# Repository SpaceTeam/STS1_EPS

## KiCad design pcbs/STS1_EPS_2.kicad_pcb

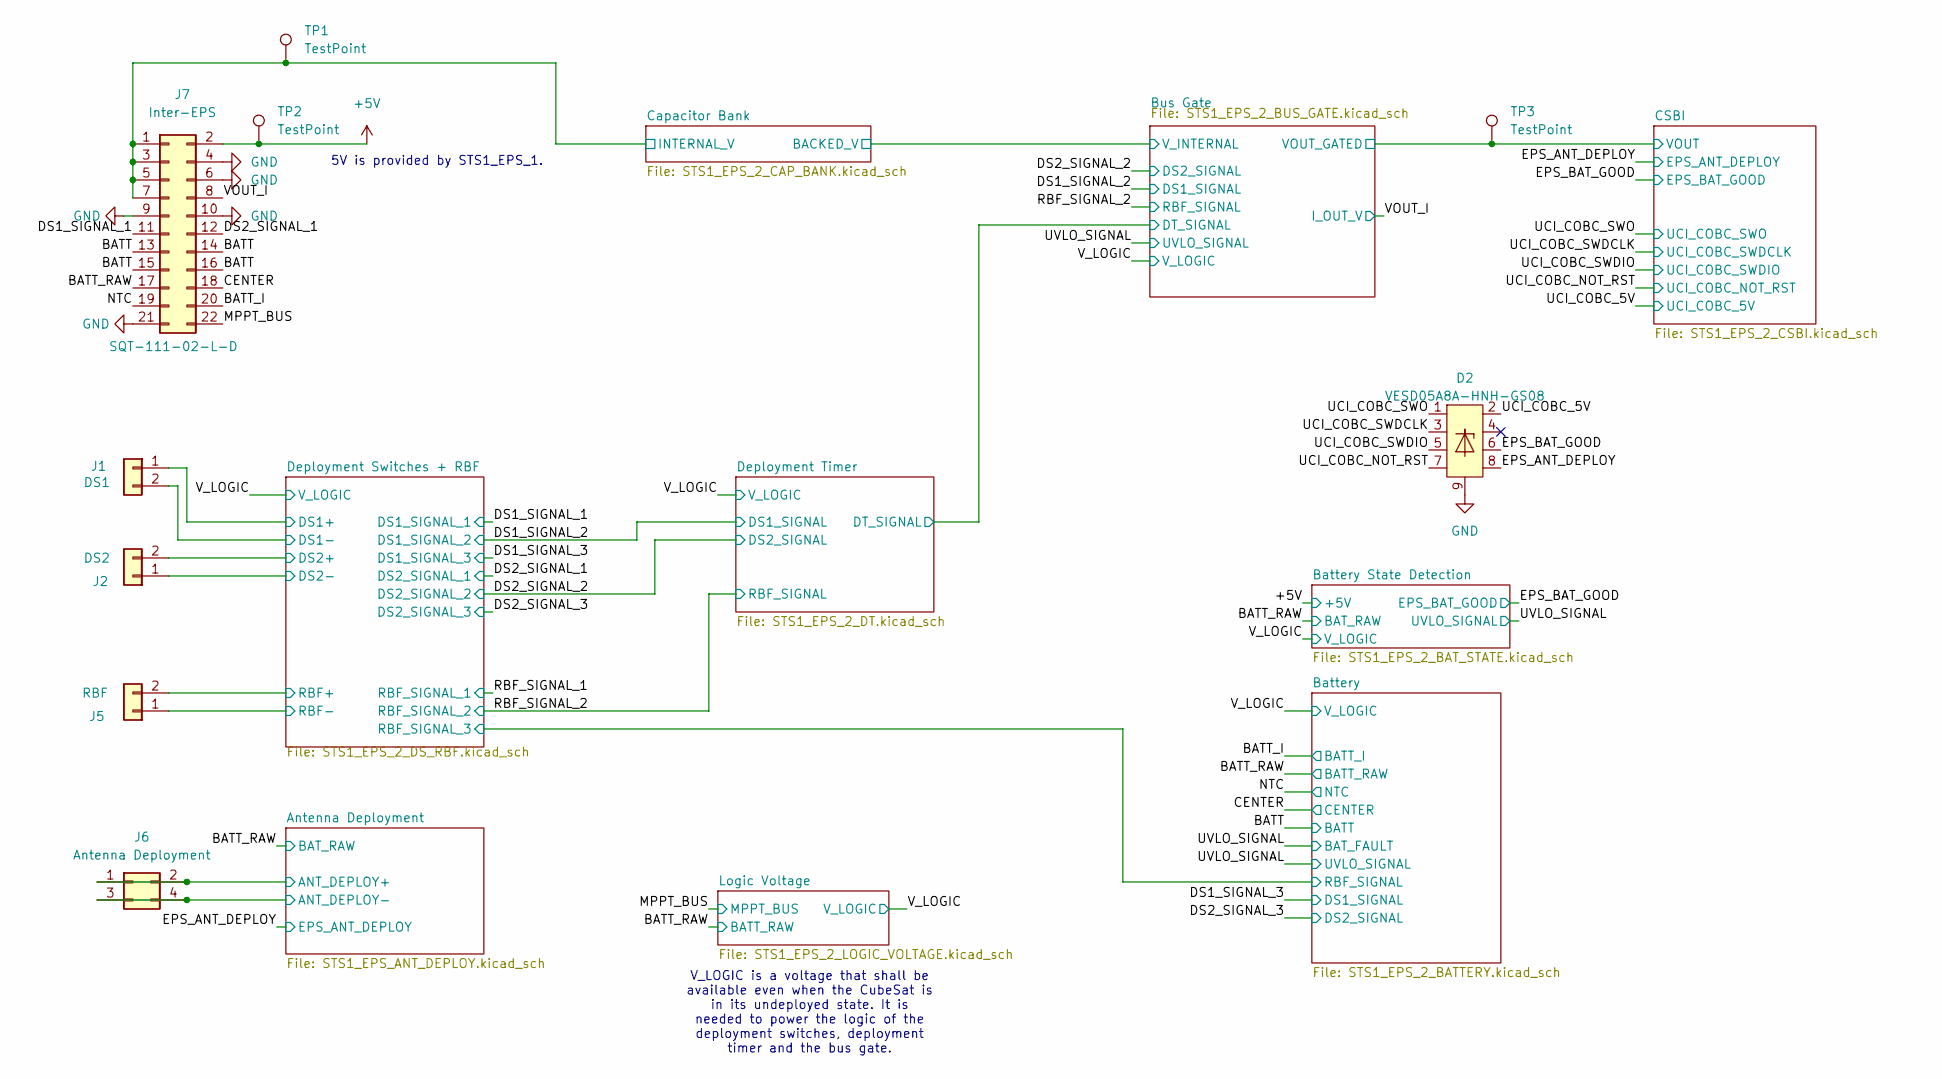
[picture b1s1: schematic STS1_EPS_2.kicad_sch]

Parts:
D2: VESD05A8A-HNH-GS08; LLP1713-9L
J1: DS1; M808420245; Part Nr. M80-8420245
J2: DS2; M808420245; Part Nr. M80-8420245
J5: RBF; M808420245; Part Nr. M808420245
J6: Antenna Deployment; SAMTEC_T1M-04-X-SV-L; Part Nr. SAMTEC T1M-04-X-SV-L
J7: Inter-EPS; PinHeader_2x11_P2.00mm_Vertical; Part# SQT-111-02-L-D
TP1, TP2, TP3: TestPoint; TestPoint_THTPad_D1.0mm_Drill0.5mm

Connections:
+5V: J7.2, TP2.1 (1_1); also elsewhere on the board
/Antenna Deployment/ANT_DEPLOY-: J6.3, J6.4; also elsewhere on the board
/BATT: J7.13, J7.14, J7.15, J7.16; also elsewhere on the board
/BATT_I: J7.20; also elsewhere on the board
/BATT_RAW: J6.1, J6.2, J7.17; also elsewhere on the board
/Bus Gate/VOUT_GATED: TP3.1 (1_1); also elsewhere on the board
/Bus Gate/V_INTERNAL: J7.1, J7.3, J7.5, J7.7, TP1.1 (1_1); also elsewhere on the board
/CENTER: J7.18; also elsewhere on the board
/DS1_SIGNAL_1: J7.11; also elsewhere on the board
/DS2_SIGNAL_1: J7.12; also elsewhere on the board
/Deployment Switches + RBF/DS1+: J1.1; also elsewhere on the board
/Deployment Switches + RBF/DS2+: J2.2; also elsewhere on the board
/Deployment Switches + RBF/RBF-: J5.1; also elsewhere on the board
/EPS_ANT_DEPLOY: D2.8; also elsewhere on the board
/EPS_BAT_GOOD: D2.6; also elsewhere on the board
/MPPT_BUS: J7.22; also elsewhere on the board
/NTC: J7.19; also elsewhere on the board
/UCI_COBC_5V: D2.2; also elsewhere on the board
/UCI_COBC_NOT_RST: D2.7; also elsewhere on the board
/UCI_COBC_SWDCLK: D2.3; also elsewhere on the board
/UCI_COBC_SWDIO: D2.5; also elsewhere on the board
/UCI_COBC_SWO: D2.1; also elsewhere on the board
/VOUT_I: J7.8; also elsewhere on the board
/V_LOGIC: J5.2; also elsewhere on the board
GND: D2.9, J1.2, J2.1, J7.4, J7.6, J7.9, J7.10, J7.21; also elsewhere on the board

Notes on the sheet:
5V is provided by STS1_EPS_1.
V_LOGIC is a voltage that shall be available even when the CubeSat is in its undeployed state. It is needed to power the logic of the deployment switches, deployment timer and the bus gate.

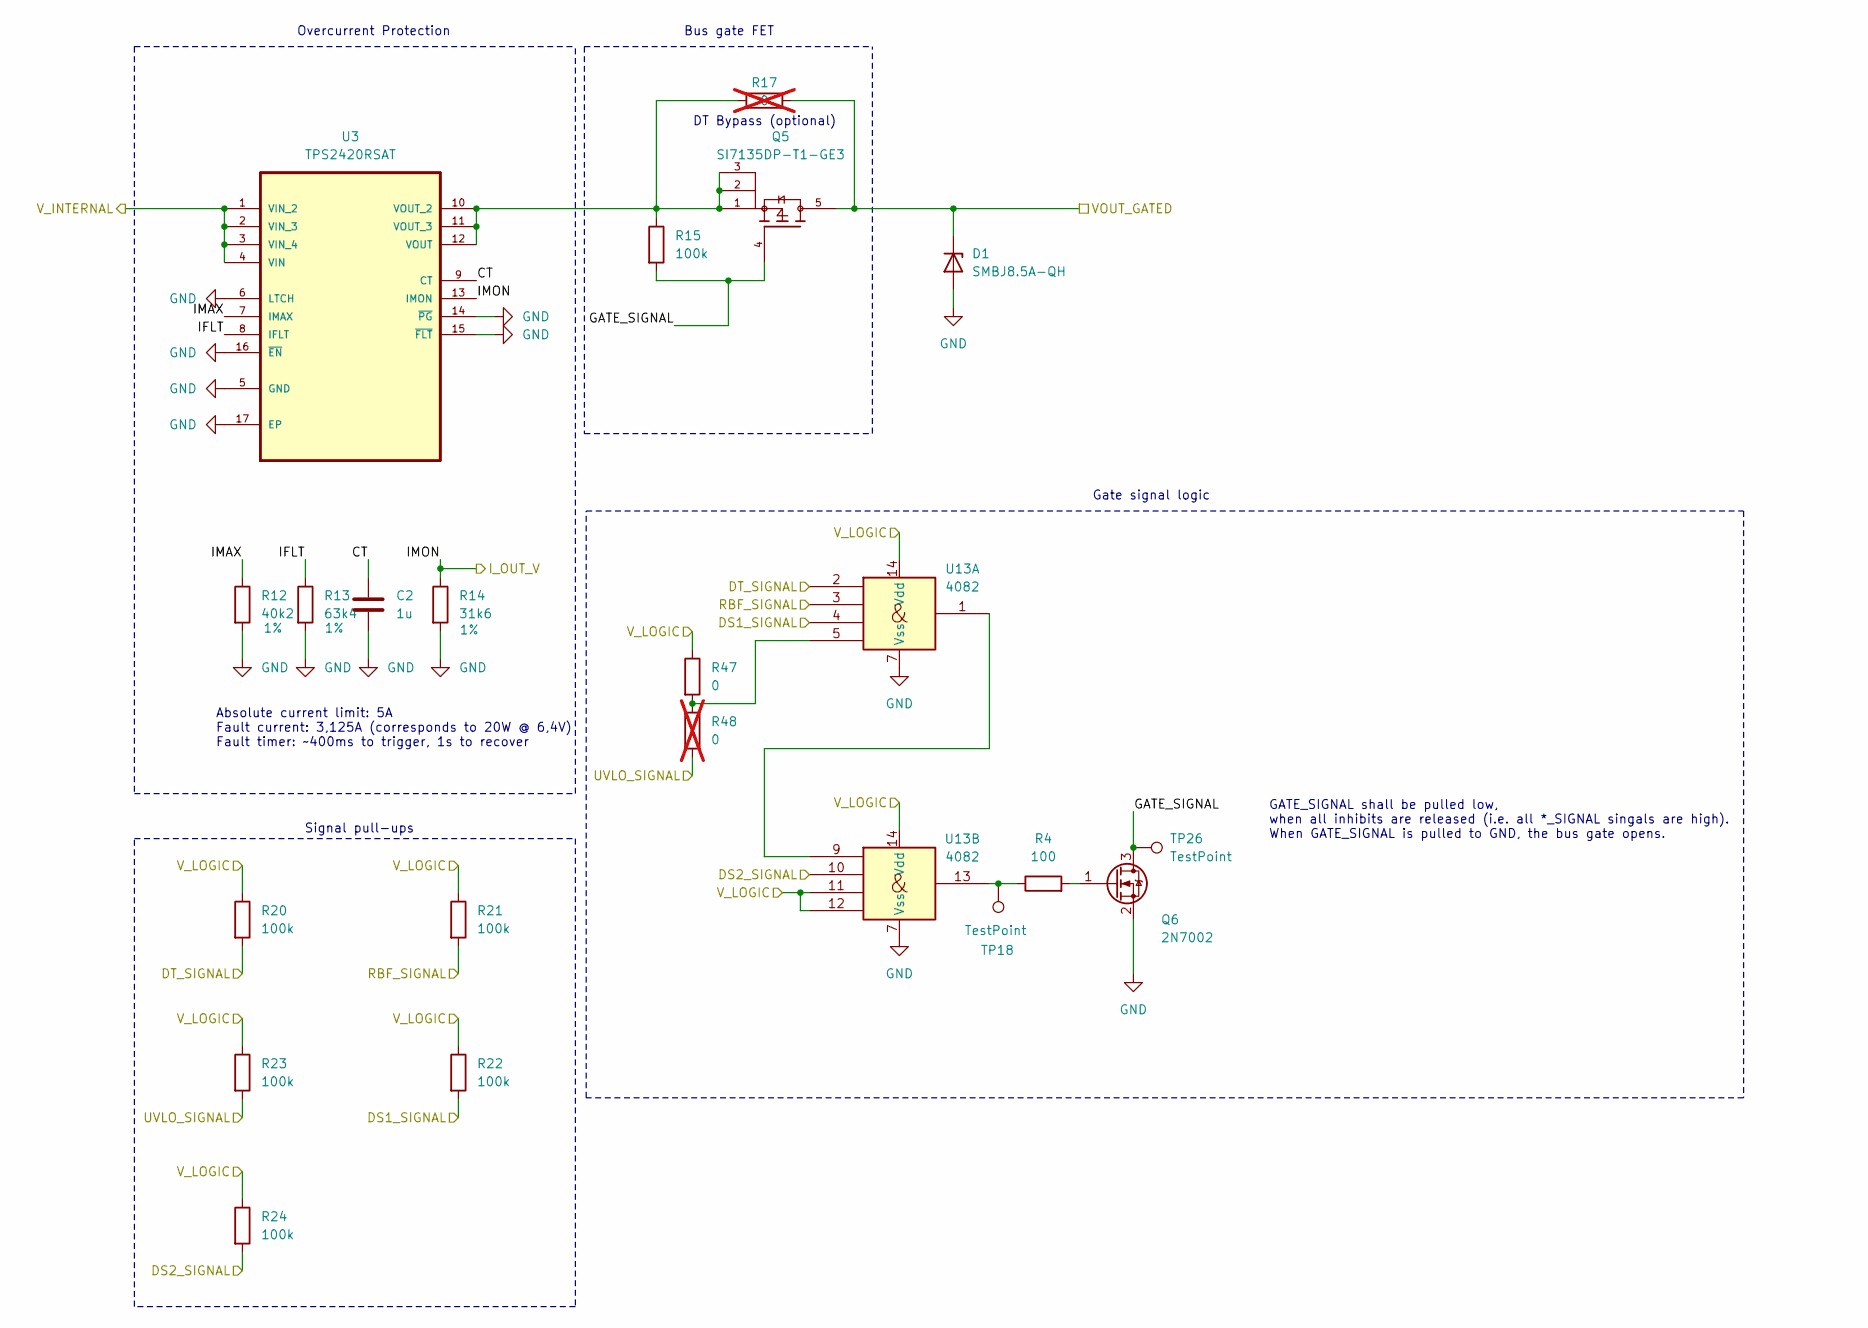
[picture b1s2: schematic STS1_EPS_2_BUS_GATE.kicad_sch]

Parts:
C2: 1u; C_0805_2012Metric; Part Nr. C0805T105K4RALTU
D1: SMBJ8.5A-QH; D_SMB
Q5: SI7135DP-T1-GE3; POWERPAK_SO8_single; PARTREV A
Q6: 2N7002; SOT-23
R4: 100; R_0805_2012Metric; Part Nr. TNPW0805100RFETA
R12: 40k2; R_0805_2012Metric; Tolerance 1%; Part Nr. CPF0805B40K2E1
R13: 63k4; R_0805_2012Metric; Tolerance 1%; Part Nr. RN73R2ATTD6342B25
R14: 31k6; R_0805_2012Metric; Tolerance 1%; Part Nr. ERA-6ARB3162V
R15, R20, R21, R22, R23, R24: 100k; R_0805_2012Metric; Part Nr. TNPW0805100KFEEA
R17, R48: 0; R_0805_2012Metric; not fitted
R47: 0; R_0805_2012Metric
TP18, TP26: TestPoint; TestPoint_THTPad_D1.0mm_Drill0.5mm
U3: TPS2420RSAT; QFN65P400X400X100-17N; MPN TPS2420RSAT
U13: 4082; SOIC-14_3.9x8.7mm_P1.27mm; Part Nr. HEF4082BT-Q100J

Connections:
/Bus Gate/CT: C2.1, U3.9 (CT)
/Bus Gate/DT_SIGNAL: R20.2, U13.2; also elsewhere on the board
/Bus Gate/GATE_SIGNAL: Q5.4, Q6.3 (D), R15.2, TP26.1 (1_1)
/Bus Gate/IFLT: R13.1, U3.8 (IFLT)
/Bus Gate/IMAX: R12.1, U3.7 (IMAX)
/Bus Gate/VOUT_GATED: D1.1 (K), Q5.5, R17.2; also elsewhere on the board
/Bus Gate/V_INTERNAL: U3.1 (VIN_2), U3.2 (VIN_3), U3.3 (VIN_4), U3.4 (VIN); also elsewhere on the board
/DS1_SIGNAL_2: R22.2, U13.4; also elsewhere on the board
/DS2_SIGNAL_2: R24.2, U13.10; also elsewhere on the board
/RBF_SIGNAL_2: R21.2, U13.3; also elsewhere on the board
/UVLO_SIGNAL: R23.2, R48.2; also elsewhere on the board
/VOUT_I: R14.1, U3.13 (IMON); also elsewhere on the board
/V_LOGIC: R20.1, R21.1, R22.1, R23.1, R24.1, R47.1, U13.11, U13.12, U13.14 (Vdd); also elsewhere on the board
GND: C2.2, D1.2 (A), Q6.2 (S), R12.2, R13.2, R14.2, U3.5 (GND), U3.6 (LTCH), U3.14 (~PG), U3.15 (~FLT), U3.16 (~EN), U3.17 (EP), U13.7 (Vss); also elsewhere on the board
unnamed: Q6.1 (G), R4.2
unnamed: R4.1, TP18.1 (1_1), U13.13
unnamed: R47.2, R48.1, U13.5
unnamed: Q5.1, Q5.2, Q5.3, R15.1, R17.1, U3.10 (VOUT_2), U3.11 (VOUT_3), U3.12 (VOUT)
unnamed: U13.1, U13.9

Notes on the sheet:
Signal pull-ups
Gate signal logic
Overcurrent Protection
Bus gate FET
Absolute current limit: 5A Fault current: 3,125A (corresponds to 20W @ 6,4V) Fault timer: ~400ms to trigger, 1s to recover
DT Bypass (optional)
GATE_SIGNAL shall be pulled low, when all inhibits are released (i.e. all *_SIGNAL singals are high). When GATE_SIGNAL is pulled to GND, the bus gate opens.

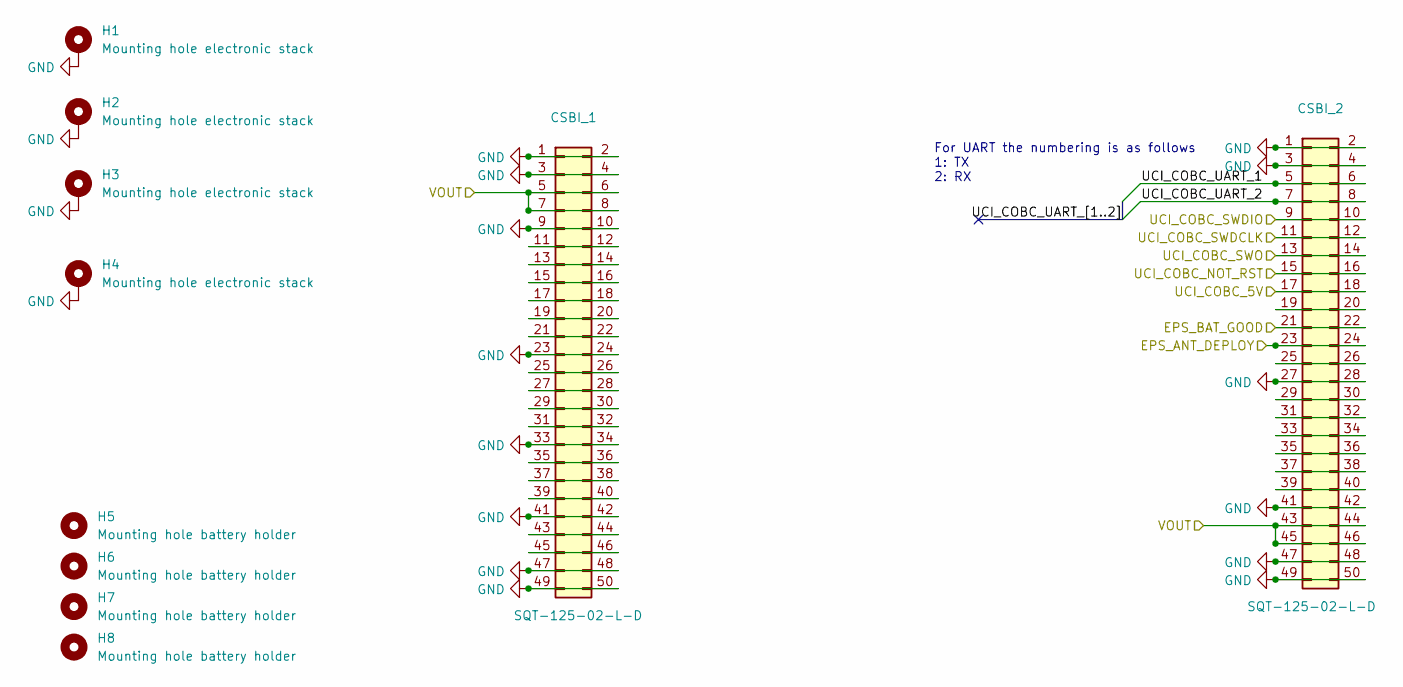
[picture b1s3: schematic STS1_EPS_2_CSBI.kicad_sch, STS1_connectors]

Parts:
CSBI_1, CSBI_2: PinHeader_2x25_P2.00mm_Vertical; Part # SQT-125-02-L-D
H1, H2, H3, H4: Mounting hole electronic stack; MountingHole_4.3mm_M4_Pad_Via
H5, H6, H7, H8: Mounting hole battery holder; MountingHole_2.2mm_M2

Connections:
/Bus Gate/VOUT_GATED: CSBI_1.5, CSBI_1.6, CSBI_1.7, CSBI_1.8, CSBI_2.43, CSBI_2.44, CSBI_2.45, CSBI_2.46; also elsewhere on the board
/CSBI/UCI_COBC_UART_1: CSBI_2.5, CSBI_2.6
/CSBI/UCI_COBC_UART_2: CSBI_2.7, CSBI_2.8
/EPS_ANT_DEPLOY: CSBI_2.23, CSBI_2.24; also elsewhere on the board
/EPS_BAT_GOOD: CSBI_2.21, CSBI_2.22; also elsewhere on the board
/UCI_COBC_5V: CSBI_2.17, CSBI_2.18; also elsewhere on the board
/UCI_COBC_NOT_RST: CSBI_2.15, CSBI_2.16; also elsewhere on the board
/UCI_COBC_SWDCLK: CSBI_2.11, CSBI_2.12; also elsewhere on the board
/UCI_COBC_SWDIO: CSBI_2.9, CSBI_2.10; also elsewhere on the board
/UCI_COBC_SWO: CSBI_2.13, CSBI_2.14; also elsewhere on the board
GND: CSBI_1.1, CSBI_1.2, CSBI_1.3, CSBI_1.4, CSBI_1.9, CSBI_1.10, CSBI_1.23, CSBI_1.24, CSBI_1.33, CSBI_1.34, CSBI_1.41, CSBI_1.42, CSBI_1.47, CSBI_1.48, CSBI_1.49, CSBI_1.50, CSBI_2.1, CSBI_2.2, CSBI_2.3, CSBI_2.4, CSBI_2.27, CSBI_2.28, CSBI_2.41, CSBI_2.42, CSBI_2.47, CSBI_2.48, CSBI_2.49, CSBI_2.50, H1.1 (1_1), H2.1 (1_1), H3.1 (1_1), H4.1 (1_1); also elsewhere on the board
unnamed: CSBI_1.11, CSBI_1.12
unnamed: CSBI_1.13, CSBI_1.14
unnamed: CSBI_1.15, CSBI_1.16
unnamed: CSBI_1.17, CSBI_1.18
unnamed: CSBI_1.19, CSBI_1.20
unnamed: CSBI_1.21, CSBI_1.22
unnamed: CSBI_1.25, CSBI_1.26
unnamed: CSBI_1.27, CSBI_1.28
unnamed: CSBI_1.29, CSBI_1.30
unnamed: CSBI_1.31, CSBI_1.32
unnamed: CSBI_1.35, CSBI_1.36
unnamed: CSBI_1.37, CSBI_1.38
unnamed: CSBI_1.39, CSBI_1.40
unnamed: CSBI_1.43, CSBI_1.44
unnamed: CSBI_1.45, CSBI_1.46
unnamed: CSBI_2.19, CSBI_2.20
unnamed: CSBI_2.25, CSBI_2.26
unnamed: CSBI_2.29, CSBI_2.30
unnamed: CSBI_2.31, CSBI_2.32
unnamed: CSBI_2.33, CSBI_2.34
unnamed: CSBI_2.35, CSBI_2.36
unnamed: CSBI_2.37, CSBI_2.38
unnamed: CSBI_2.39, CSBI_2.40

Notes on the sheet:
For UART the numbering is as follows 1: TX 2: RX

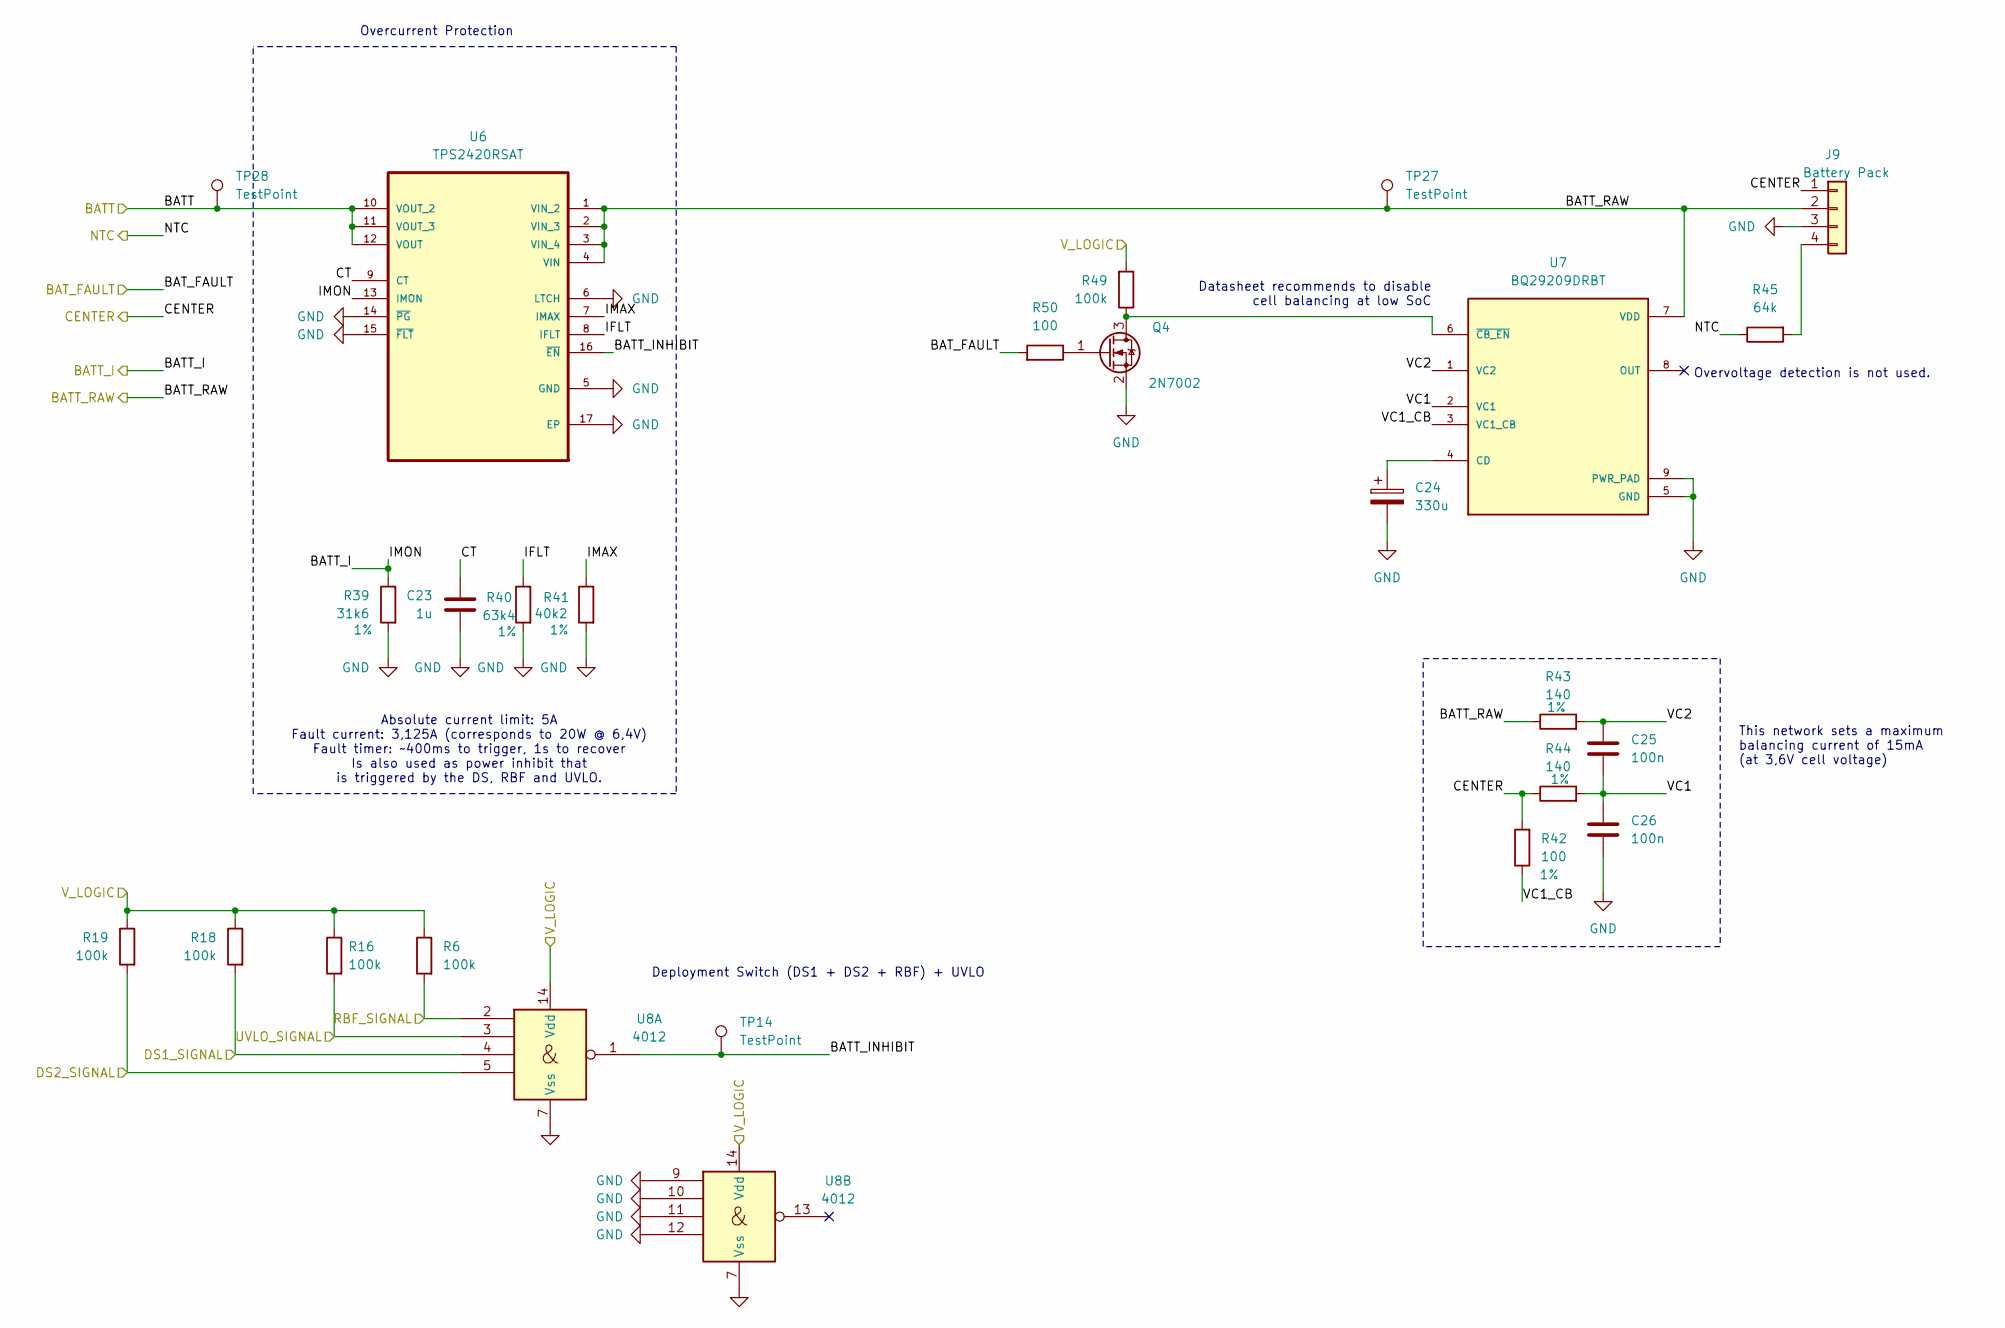
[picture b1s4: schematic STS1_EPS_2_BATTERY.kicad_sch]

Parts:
C23: 1u; C_0805_2012Metric; Part Nr. C0805T105K4RALTU
C24: 330u; CP_EIA-7343-43_Kemet-X; Part Nr. TPSE687M010R0150V
C25, C26: 100n; C_0805_2012Metric; Part Nr. C0805T104K1RCLTU
J9: Battery Pack; MOLEX_2078430004; Part MOLEX KK Plus 250 Header
Q4: 2N7002; SOT-23; Part Nr. 2N7002
R6, R16, R18, R19, R49: 100k; R_0805_2012Metric; Part Nr. TNPW0805100KFEEA
R39: 31k6; R_0805_2012Metric; Tolerance 1%; Part Nr. ERA-6ARB3162V
R40: 63k4; R_0805_2012Metric; Tolernace 1%; Part Nr. RN73R2ATTD6342B25
R41: 40k2; R_0805_2012Metric; Tolerance 1%; Part Nr. CPF0805B40K2E1
R42: 100; R_0805_2012Metric; Tolerance 1%; Part Nr. TNPW0805100RFETA
R43, R44: 140; R_0805_2012Metric; Tolerance 1%; Part Nr. TNPW0805140RBEEN
R45: 64k; R_0805_2012Metric; Part Nr. PTN0805E6422BST1
R50: 100; R_0805_2012Metric; Part Nr. TNPW0805100RFETA
TP14, TP27, TP28: TestPoint; TestPoint_THTPad_D1.0mm_Drill0.5mm
U6: TPS2420RSAT; QFN65P400X400X100-17N; MPN TPS2420RSAT
U7: BQ29209DRBT; TI_VSON8; PARTREV C
U8: 4012; SOIC-14_3.9x8.7mm_P1.27mm; Part Nr. CD4012B

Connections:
/BATT: TP28.1 (1_1), U6.10 (VOUT_2), U6.11 (VOUT_3), U6.12 (VOUT); also elsewhere on the board
/BATT_I: R39.1, U6.13 (IMON); also elsewhere on the board
/BATT_RAW: J9.2, R43.1, TP27.1 (1_1), U6.1 (VIN_2), U6.2 (VIN_3), U6.3 (VIN_4), U6.4 (VIN), U7.7 (VDD); also elsewhere on the board
/Battery/BATT_INHIBIT: TP14.1 (1_1), U6.16 (~EN), U8.1
/Battery/CT: C23.1, U6.9 (CT)
/Battery/IFLT: R40.1, U6.8 (IFLT)
/Battery/IMAX: R41.1, U6.7 (IMAX)
/Battery/RBF_SIGNAL: R6.2, U8.2; also elsewhere on the board
/Battery/VC1: C25.2, C26.1, R44.2, U7.2 (VC1)
/Battery/VC1_CB: R42.1, U7.3 (VC1_CB)
/Battery/VC2: C25.1, R43.2, U7.1 (VC2)
/CENTER: J9.1, R42.2, R44.1; also elsewhere on the board
/DS1_SIGNAL_3: R18.2, U8.4; also elsewhere on the board
/DS2_SIGNAL_3: R19.2, U8.5; also elsewhere on the board
/NTC: R45.1; also elsewhere on the board
/UVLO_SIGNAL: R16.2, R50.2, U8.3; also elsewhere on the board
/V_LOGIC: R6.1, R16.1, R18.1, R19.1, R49.2, U8.14 (Vdd); also elsewhere on the board
GND: C23.2, C24.2, C26.2, J9.3, Q4.2 (S), R39.2, R40.2, R41.2, U6.5 (GND), U6.6 (LTCH), U6.14 (~PG), U6.15 (~FLT), U6.17 (EP), U7.5 (GND), U7.9 (PWR_PAD), U8.7 (Vss), U8.9, U8.10, U8.11, U8.12; also elsewhere on the board
unnamed: J9.4, R45.2
unnamed: Q4.3 (D), R49.1, U7.6 (~CB_EN)
unnamed: Q4.1 (G), R50.1
unnamed: C24.1, U7.4 (CD)

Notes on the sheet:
Datasheet recommends to disable cell balancing at low SoC
Absolute current limit: 5A Fault current: 3,125A (corresponds to 20W @ 6,4V) Fault timer: ~400ms to trigger, 1s to recover Is also used as power inhibit that is triggered by the DS, RBF and UVLO.
This network sets a maximum balancing current of 15mA (at 3,6V cell voltage)
Overcurrent Protection
Deployment Switch (DS1 + DS2 + RBF) + UVLO
Overvoltage detection is not used.

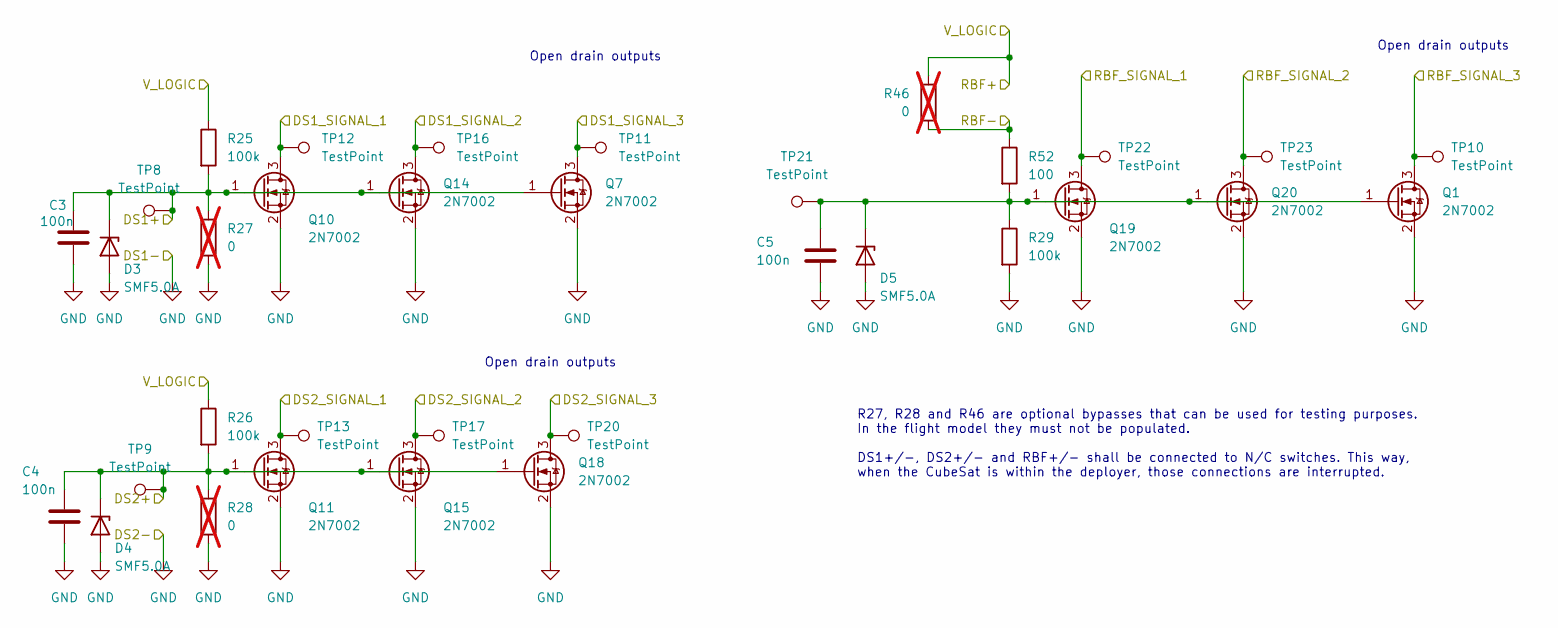
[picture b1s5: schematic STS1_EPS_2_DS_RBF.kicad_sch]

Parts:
C3, C4, C5: 100n; C_0805_2012Metric; Part Nr. C0805T104K1RCLTU
D3, D4, D5: SMF5.0A; D_SMF
Q1, Q7, Q10, Q11, Q14, Q15, Q18, Q19, Q20: 2N7002; SOT-23
R25, R26, R29: 100k; R_0805_2012Metric; Part Nr. TNPW0805100KFEEA
R27, R28, R46: 0; R_0805_2012Metric; not fitted
R52: 100; R_0805_2012Metric; Part Nr. TNPW0805100RFETA
TP8, TP9, TP10, TP11, TP12, TP13, TP16, TP17, TP20, TP21, TP22, TP23: TestPoint; TestPoint_THTPad_D1.0mm_Drill0.5mm

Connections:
/Battery/RBF_SIGNAL: Q1.3 (D), TP10.1 (1_1); also elsewhere on the board
/DS1_SIGNAL_1: Q10.3 (D), TP12.1 (1_1); also elsewhere on the board
/DS1_SIGNAL_2: Q14.3 (D), TP16.1 (1_1); also elsewhere on the board
/DS1_SIGNAL_3: Q7.3 (D), TP11.1 (1_1); also elsewhere on the board
/DS2_SIGNAL_1: Q11.3 (D), TP13.1 (1_1); also elsewhere on the board
/DS2_SIGNAL_2: Q15.3 (D), TP17.1 (1_1); also elsewhere on the board
/DS2_SIGNAL_3: Q18.3 (D), TP20.1 (1_1); also elsewhere on the board
/Deployment Switches + RBF/DS1+: C3.1, D3.1 (K), Q7.1 (G), Q10.1 (G), Q14.1 (G), R25.2, R27.1, TP8.1 (1_1); also elsewhere on the board
/Deployment Switches + RBF/DS2+: C4.1, D4.1 (K), Q11.1 (G), Q15.1 (G), Q18.1 (G), R26.2, R28.1, TP9.1 (1_1); also elsewhere on the board
/Deployment Switches + RBF/RBF-: R46.1, R52.1; also elsewhere on the board
/RBF_SIGNAL_1: Q19.3 (D), TP22.1 (1_1)
/RBF_SIGNAL_2: Q20.3 (D), TP23.1 (1_1); also elsewhere on the board
/V_LOGIC: R25.1, R26.1, R46.2; also elsewhere on the board
GND: C3.2, C4.2, C5.2, D3.2 (A), D4.2 (A), D5.2 (A), Q1.2 (S), Q7.2 (S), Q10.2 (S), Q11.2 (S), Q14.2 (S), Q15.2 (S), Q18.2 (S), Q19.2 (S), Q20.2 (S), R27.2, R28.2, R29.2; also elsewhere on the board
unnamed: C5.1, D5.1 (K), Q1.1 (G), Q19.1 (G), Q20.1 (G), R29.1, R52.2, TP21.1 (1_1)

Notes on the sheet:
Open drain outputs
R27, R28 and R46 are optional bypasses that can be used for testing purposes. In the flight model they must not be populated. DS1+/-, DS2+/- and RBF+/- shall be connected to N/C switches. This way, when the CubeSat is within the deployer, those connections are interrupted.

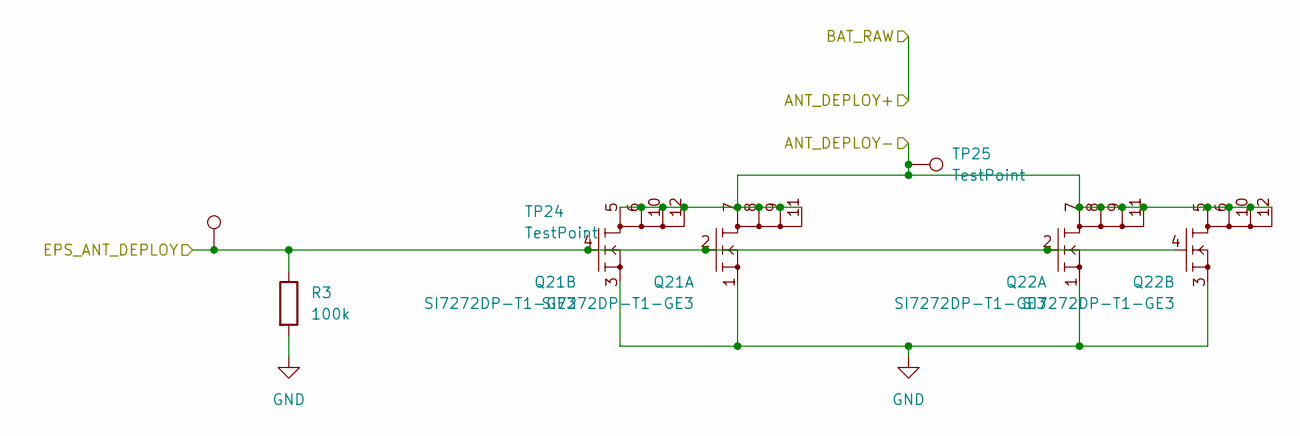
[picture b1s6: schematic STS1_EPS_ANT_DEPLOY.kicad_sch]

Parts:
Q21, Q22: SI7272DP-T1-GE3; POWERPAK_SO8
R3: 100k; R_0805_2012Metric; Part Nr. TNPW0805100KFEEA
TP24, TP25: TestPoint; TestPoint_THTPad_D1.0mm_Drill0.5mm

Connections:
/Antenna Deployment/ANT_DEPLOY-: Q21.5 (D2_1), Q21.6 (D2_2), Q21.7 (D1_1), Q21.8 (D1_2), Q21.9 (D1_3), Q21.10 (D2_3), Q21.11 (D1_4), Q21.12 (D2_4), Q22.5 (D2_1), Q22.6 (D2_2), Q22.7 (D1_1), Q22.8 (D1_2), Q22.9 (D1_3), Q22.10 (D2_3), Q22.11 (D1_4), Q22.12 (D2_4), TP25.1 (1_1); also elsewhere on the board
/EPS_ANT_DEPLOY: Q21.2 (G1), Q21.4 (G2), Q22.2 (G1), Q22.4 (G2), R3.1, TP24.1 (1_1); also elsewhere on the board
GND: Q21.1 (S1), Q21.3 (S2), Q22.1 (S1), Q22.3 (S2), R3.2; also elsewhere on the board

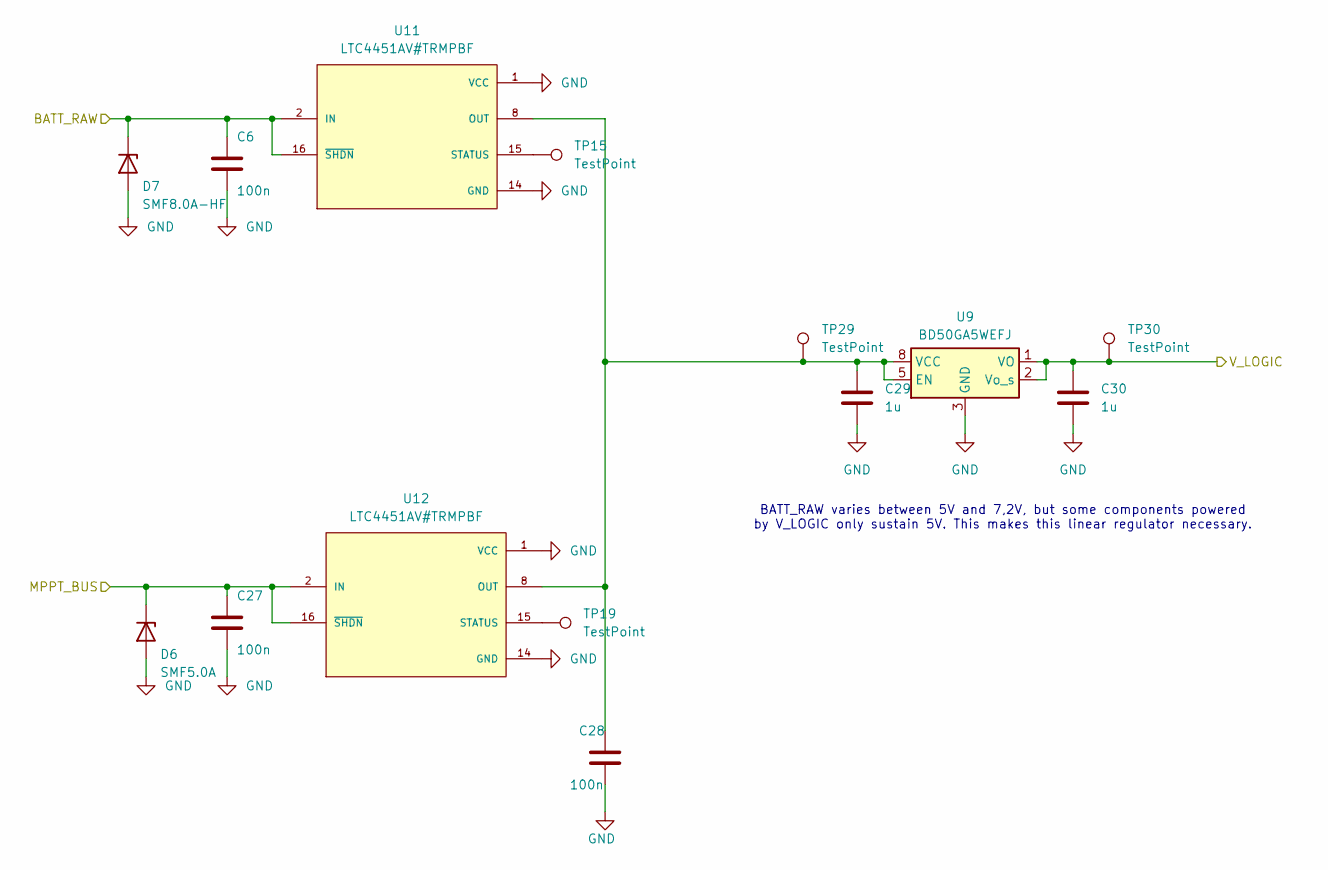
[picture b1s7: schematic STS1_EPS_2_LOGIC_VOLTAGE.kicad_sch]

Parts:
C6, C27, C28: 100n; C_0805_2012Metric; Part Nr. C0805T104K1RCLTU
C29, C30: 1u; C_0805_2012Metric; Part Nr. C0805T105K4RALTU
D6: SMF5.0A; D_SMF
D7: SMF8.0A-HF; D_SOD-123F
TP15, TP19, TP29, TP30: TestPoint; TestPoint_THTPad_D1.0mm_Drill0.5mm
U9: BD50GA5WEFJ; HTSOP-8-1EP_3.9x4.9mm_P1.27mm_EP2.4x3.2mm
U11, U12: LTC4451AV#TRMPBF; AD_LQFN-16; PARTREV 0

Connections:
/BATT_RAW: C6.1, D7.1 (K), U11.2 (IN), U11.16 (~SHDN); also elsewhere on the board
/MPPT_BUS: C27.1, D6.1 (K), U12.2 (IN), U12.16 (~SHDN); also elsewhere on the board
/V_LOGIC: C30.1, TP30.1 (1_1), U9.1 (VO), U9.2 (Vo_s); also elsewhere on the board
GND: C6.2, C27.2, C28.2, C29.2, C30.2, D6.2 (A), D7.2 (A), U9.3 (GND), U9.4 (GND), U9.6 (GND), U9.7 (GND), U9.9 (GND), U11.1 (VCC), U11.14 (GND), U12.1 (VCC), U12.14 (GND); also elsewhere on the board
unnamed: C28.1, C29.1, TP29.1 (1_1), U9.5 (EN), U9.8 (VCC), U11.8 (OUT), U12.8 (OUT)
unnamed: TP15.1 (1_1), U11.15 (STATUS)
unnamed: TP19.1 (1_1), U12.15 (STATUS)

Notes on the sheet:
BATT_RAW varies between 5V and 7,2V, but some components powered by V_LOGIC only sustain 5V. This makes this linear regulator necessary.

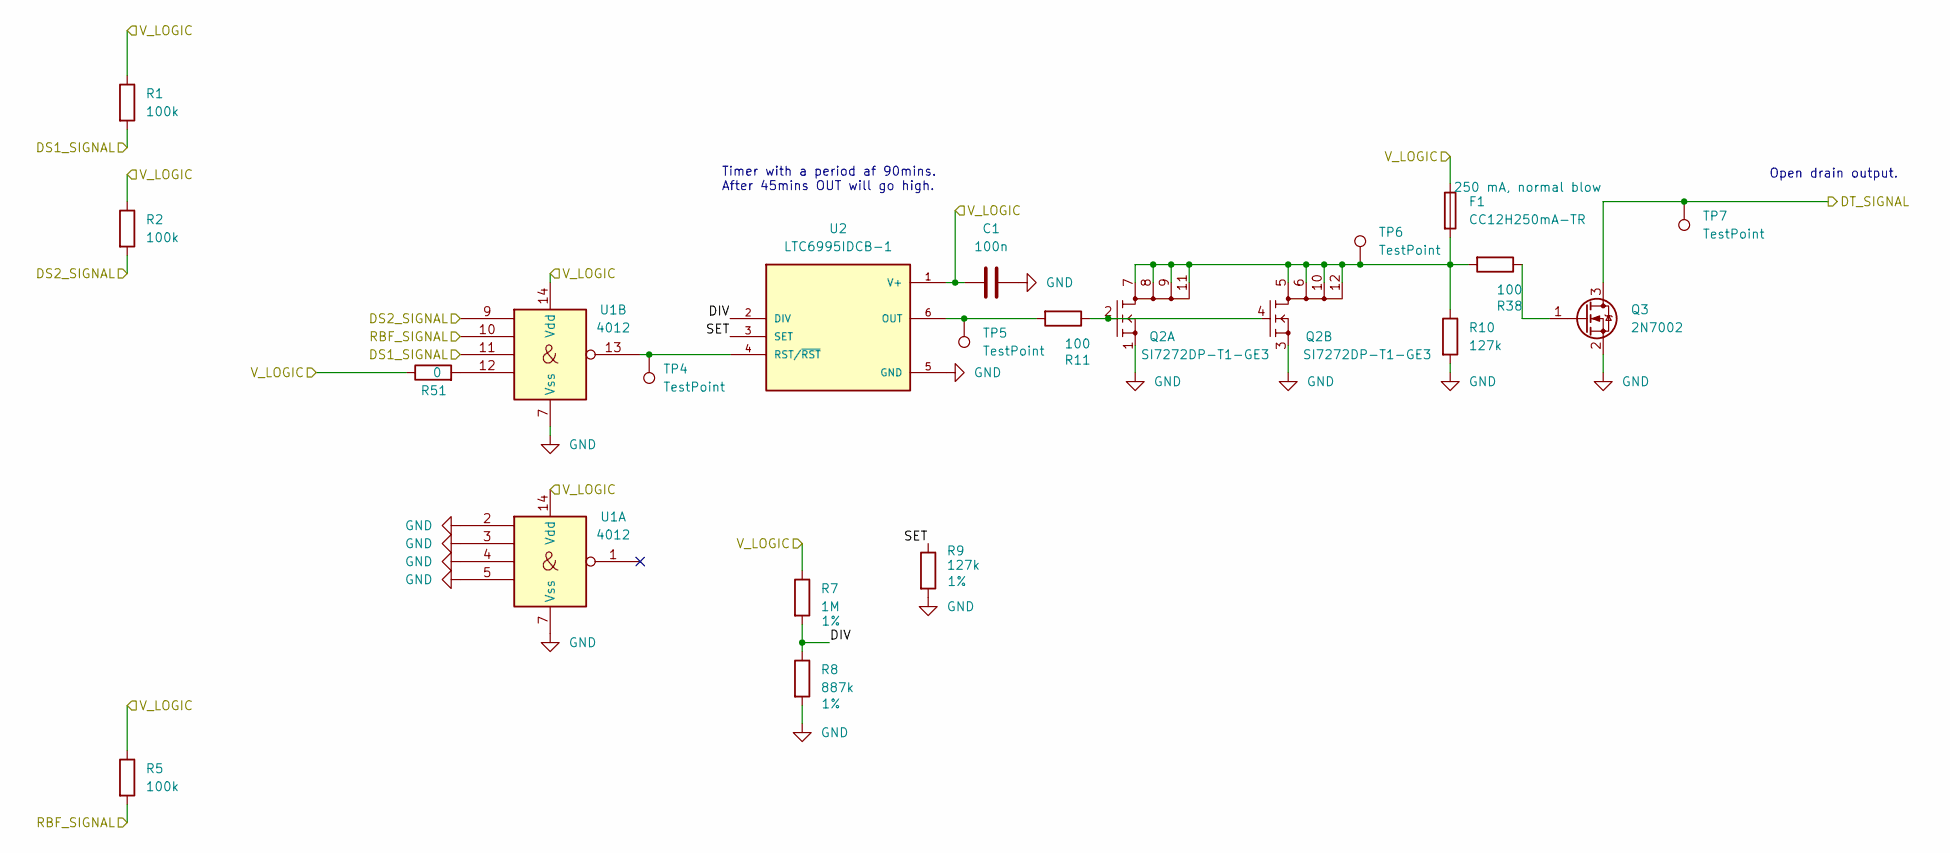
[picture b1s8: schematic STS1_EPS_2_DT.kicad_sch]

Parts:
C1: 100n; C_0805_2012Metric; Part Nr. C0805T104K1RCLTU
F1: CC12H250mA-TR; R_1206_3216Metric
Q2: SI7272DP-T1-GE3; POWERPAK_SO8
Q3: 2N7002; SOT-23
R1, R2, R5: 100k; R_0805_2012Metric; Part Nr. TNPW0805100KFEEA
R7: 1M; R_0805_2012Metric; Tolerance 1%; Part Nr. CRT0805-BY-1004ELF
R8: 887k; R_0805_2012Metric; Tolerance 1%; Part Nr. ERA-6AEB8873V
R9: 127k; R_0805_2012Metric; Tolerance 1%; Part Nr. RN73H2ATTD1273B25
R10: 127k; R_0805_2012Metric; Part Nr. RN73H2ATTD1273B25
R11, R38: 100; R_0805_2012Metric; Part Nr. TNPW0805100RFETA
R51: 0; R_0805_2012Metric; Tolerance 1%
TP4, TP5, TP6, TP7: TestPoint; TestPoint_THTPad_D1.0mm_Drill0.5mm
U1: 4012; SOIC-14_3.9x8.7mm_P1.27mm; Part Nr. CD4012B
U2: LTC6995IDCB-1; DFN-6-1EP_3x2mm_P0.5mm_EP1.65x1.35mm; PARTREV Rev. B

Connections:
/Bus Gate/DT_SIGNAL: Q3.3 (D), TP7.1 (1_1); also elsewhere on the board
/DS1_SIGNAL_2: R1.2, U1.11; also elsewhere on the board
/DS2_SIGNAL_2: R2.2, U1.9; also elsewhere on the board
/Deployment Timer/DIV: R7.2, R8.1, U2.2 (DIV)
/Deployment Timer/SET: R9.1, U2.3 (SET)
/RBF_SIGNAL_2: R5.2, U1.10; also elsewhere on the board
/V_LOGIC: C1.1, F1.1, R1.1, R2.1, R5.1, R7.1, R51.1, U1.14 (Vdd), U2.1 (V+); also elsewhere on the board
GND: C1.2, Q2.1 (S1), Q2.3 (S2), Q3.2 (S), R8.2, R9.2, R10.2, U1.2, U1.3, U1.4, U1.5, U1.7 (Vss), U2.5 (GND), U2.7 (GND); also elsewhere on the board
unnamed: F1.2, Q2.5 (D2_1), Q2.6 (D2_2), Q2.7 (D1_1), Q2.8 (D1_2), Q2.9 (D1_3), Q2.10 (D2_3), Q2.11 (D1_4), Q2.12 (D2_4), R10.1, R38.2, TP6.1 (1_1)
unnamed: Q2.2 (G1), Q2.4 (G2), R11.1
unnamed: Q3.1 (G), R38.1
unnamed: R51.2, U1.12
unnamed: R11.2, TP5.1 (1_1), U2.6 (OUT)
unnamed: TP4.1 (1_1), U1.13, U2.4 (RST/~RST)

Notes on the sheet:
Timer with a period af 90mins. After 45mins OUT will go high.
Open drain output.

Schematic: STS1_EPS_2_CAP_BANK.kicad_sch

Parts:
C7, C11, C14, C17, C20: 680u; CP_EIA-7343-43_Kemet-X; Part Nr. TPSE687M010R0150V
C8, C9, C10, C12, C13, C15, C16, C18, C19, C21, C22: 680n; C_0805_2012Metric; Part Nr. C0805T684K5RCLTM

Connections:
/Bus Gate/V_INTERNAL: C7.1, C8.1, C9.1, C10.1, C11.1, C12.1, C13.1, C14.1, C15.1, C16.1, C17.1, C18.1, C19.1, C20.1, C21.1, C22.1; also elsewhere on the board
GND: C7.2, C8.2, C9.2, C10.2, C11.2, C12.2, C13.2, C14.2, C15.2, C16.2, C17.2, C18.2, C19.2, C20.2, C21.2, C22.2; also elsewhere on the board

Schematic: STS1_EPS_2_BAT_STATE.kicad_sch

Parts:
R30: 806k; R_0805_2012Metric; Tolerance 1%; Part Nr. ERA-6AEB8063V
R31, R34: 10k; R_0805_2012Metric; Tolerance 1%; Part Nr. TNPW080510K0FEEA
R32, R35: 187k; R_0805_2012Metric; Tolerance 1%; Part Nr. RN73C2A187KBTDF
R33: 590k; R_0805_2012Metric; Tolerance 1%; Part Nr. TNPW0805590KBEEA
R36, R37: 470k; R_0805_2012Metric; Part Nr. ERA-6AED474V
U4: MIC841N; SOT-353_SC-70-5
U5: MIC841H; SOT-353_SC-70-5

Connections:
+5V: R36.2, U4.5 (VDD); also elsewhere on the board
/BATT_RAW: R30.2, R33.2; also elsewhere on the board
/EPS_BAT_GOOD: R36.1, U4.4 (OUT); also elsewhere on the board
/UVLO_SIGNAL: R37.1, U5.4 (OUT); also elsewhere on the board
/V_LOGIC: R37.2, U5.5 (VDD); also elsewhere on the board
GND: R32.1, R35.1, U4.2 (GND), U5.2 (GND); also elsewhere on the board
unnamed: R31.1, R32.2, U4.1 (HTH)
unnamed: R30.1, R31.2, U4.3 (LTH)
unnamed: R34.1, R35.2, U5.1 (HTH)
unnamed: R33.1, R34.2, U5.3 (LTH)

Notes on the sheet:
This implements a hysteresis. At BAT_RAW >= 6.65V, EPS_BAT_GOOD is pulled high. If BAT_RAW decreases below <= 6.31V, EPS_BAT_GOOD is pulled low.
This implements a hysteresis. At BAT_RAW <= 5V, UVLO_SIGNAL is pulled low. If BAT_RAW increases above >= 5,3V, UVLO_SIGNAL is pulled high.
